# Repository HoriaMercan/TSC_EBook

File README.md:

## Horia Mercan - OpenBook - Systems Testing

This project presents the electronic design (schematic/pcb) and the visual design of a complete ebook. 

## Hardware Modules and Components

**ESP32-C6-WROOM-1-N8 – Main Microcontroller:**
* Power Supply: 3.3V.
* Communications: SPI, I2C, UART, GPIO.

We will link interfaces of each module with main controller's pins:

**SPI ESD Protection Lines**
* Protects the SPI lines for the SD card, e-paper, external flash.

**LDO Voltage Regulator**
* Steps down the voltage from 5V to 3.3V to power the ESP32-C6 and other modules.

**SD Card Module**
* Interface: SPI
* Pins Used:
    * `SS_SD` → `IO4`
    * `MOSI` → `IO7`
    * `MISO` → `IO2`
    * `SCK` → `IO6`

**E-Paper Display**
* Interface: SPI
* Pins Used:
    * `EPD_CS` → `IO10`
    * `EPD_DC` → `IO5`
    * `EPD_RST` → `IO23`
    * `EPD_BUSY` → `IO3`
    * `MOSI`, `SCK` (shared with SD)

**RTC Module - DS3231SN**
* Interface: I2C
* Pins Used:
    * `SCL` → `IO22`
    * `SDA` → `IO21`
    * `INT_RTC` → `IO8`
    * `32KHZ` → `IO1`
    * `RTC_RST` → `IO18`

**LiPo Fuel Gauger**
* Built-in charging control.
* MAX17048G+T10
* Battery level monitoring with:
    * Battery ChargeLevel IC → I2C => `SDA`, `SCL`

**Qwiic / Stemma QT Connector**
* Communicates entirely via I2C: `SCL`/`SDA` 

**Environmental Sensor - BME688**
* Protocol: I2C (shared) => `SDA`, `SCL`

**Environmental Sensor - BME688**
* Interface: I2C (shared with RTC)
* Power Supply: 3.3V
* Pins Used:  `SDA`, `SCL`

**External Flash - NORFlash64MB**
* Interface: SPI
* Pins Used:
    * `FLASH_CS` → `IO11`
    * Rest (`MOSI`, `MISO`, `SCK`) shared

**SD/USB interface**
* `USB_D+` → `IO13`
* `USB_D-` → `IO12`

**Reset and Boot Buttons**
* `IO/BOOT` → `IO9`
* `RESET` → `EN`

**Diodes for reverse polarity protection.**

**USB-C Connector + ESD Protection**
* Main power and data input.
* Includes TVS diodes for ESD protection.

## Block components & schematic

## Communication Interfaces

| Interface | Connected Components       | ESP32-C6 Pins                       |
| :-------- | :------------------------- | :------------------------------------ |
| SPI       | SD Card, E-paper, NOR Flash | `MOSI` (`IO7`), `MISO` (`IO2`), `SCK` (`IO6`) |
| I2C       | RTC, BME688, Battery Level | `SDA` (`IO22`), `SCL` (`IO21`)        |
| UART      | Debugging / Flash          | `TX` (`GPIO16`), `RX` (`GPIO17`)        |
| GPIO      | Buttons, status signals    | `IO0` - `IO23`                        |
| USB       | PC connection / power      | `USB_D+`/`D-` (`IO13`/`IO12`)

## Energy management

| Component                   | Power Supply (V) | Estimated Current (mA) | Estimated Power (W) | Notes                                                                  |
|-----------------------------|-------------------|------------------------|----------------------|------------------------------------------------------------------------|
| ESP32-C6-WROOM-1-N8         | 3.3               | 150 (average)          | 0.5                  | Active mode; varies significantly based on usage.                       |
| SD Card Module              | 3.3               | 10 (average)           | 0.033                | Intermittent read/write operations.                                     |
| E-Paper Display             | 3.3               | 1(average)             | 0.0033               | Power used only during updates, very low average.                   |
| RTC Module - DS3231SN       | 3.3               | 1                      | 0.0033               |                                                                        |
| LiPo Fuel Gauger (MAX17048) | 3.3               | 0.05                   | 0.000165             | Very low power consumption.                                            |
| BME688 (Environmental Sensor) | 3.3               | 1 (average)            | 0.0033               | Intermittent readings.                                                  |
| NORFlash64MB (External Flash)| 3.3               | 2 (average)            | 0.0066               | Intermittent read/write operations.                                     |
| LDO Voltage Regulator       | 5 (input) / 3.3 (output) | Variable             | Variable               | Efficiency depends on load; quiescent current is very low.             |
| USB-C Connector + ESD       | 5 (input)         | Variable               | Variable               | Power depends on charging current; ESD protection negligible.          |
| Reset/Boot Buttons          | N/A               | Negligible             | Negligible           |                                                                        |
| **Total (Approximate)** |                   |          150-200              | **~0.55** | This is a rough estimate; actual power depends on duty cycles and usage. |

## Images

# BOM

| Piece Name | Piece Type | Link |
|------------|------------|------|
| SAMACSYS_PARTS_USB4110-GF-A | USB-C Connector | https://www.snapeda.com/parts/USB4110-GF-A./Global%20Connector%20Technology/view-part/ |
| ESP32_WROVER_EAGLE-LTSPICE_R | Resistor | https://componentsearchengine.com/part-view/R0402%201%25%20100%20K%20(RC0402FR-07100KL)/YAGEO |
| MAX17048G+T10 | Cell Fuel Gauge | https://www.snapeda.com/parts/MAX17048G+T10/Analog%20Devices/view-part/ |
| W25Q512JVEIQ | Flash Memory (NOR) | https://www.snapeda.com/parts/W25Q512JVEIQ/Winbond%20Electronics/view-part/?ref=search&t=W25Q512JVEIQ |
| RCL_CPOL-EU | Polarized Capacitor | https://grabcad.com/library/tantalum-smd-capacitor-type-b-3528-1 |
| ESP32-C6-WROOM-1-N8 | ESP32 Module | https://www.snapeda.com/parts/ESP32-C6-WROOM-1-N8/Espressif%20Systems/view-part/?ref=search&t=ESP32-C6-WROOM-1-N8 |
| ADAFRUIT_CHIP-LED0603 | LED | https://www.snapeda.com/parts/KP-1608SURCK/Kingbright/view-part/?ref=search&t=LED%200603 |
| ESP32_WROVER_SPARKFUN-IC-POWER_MCP73831 | Li-Ion/Li-Poly Charge Management Controller | https://componentsearchengine.com/part-view/MCP73831T-2ACI%2FOT/Microchip |
| ESP32_WROVER_BME680_BME680 | Environmental Sensor | https://www.snapeda.com/parts/BME680/Bosch%20Sensortec/view-part/?ref=search&t=bme680 |
| CPH3225A | Crystal | https://www.snapeda.com/parts/CPH3225A/Seiko/view-part/ |
| BUTTON_CUSYOMV1 | Button | https://ro.mouser.com/ProductDetail/Panasonic/EVQ-P7L01P?qs=rJ%252BziJWpyszWhhNszc02jQ%3D%3D&utm_id=6470900573&utm_source=google&utm_medium=cpc&utm_marketing_tactic=emeacorp&gad_source=1&gbraid=0AAAAADn_wf2u1-1FzOTFyljDC4WPsSKtJ&gclid=Cj0KCQjwqcO_BhDaARIsACz62vPVeStXn6lXkpk-IPhYAE7F2gpbfTm751cNxrlbJa5xGxG5NT01Z4waAqXEEALw_wcB&_gl=1*bly5rh*_ga*NDU0NzEyMTQxLjE3NDM4Nzk4OTU.*_ga_15W4STQT4T*MTc0Mzg4MTg0Ni4yLjAuMTc0Mzg4MTg0Ny41OS4wLjA. |
| FH34SRJ-24S-0.5SH_99_ | FPC Connector | https://componentsearchengine.com/part-view/FH34SRJ-24S-0.5SH(99)/Hirose |
| 744043680 | Inductor | https://eu.mouser.com/ProductDetail/Wurth-Elektronik/744043680?qs=PGXP4M47uW6VkZq%252BkzjrHA%3D%3D |
| PGB1010603MR | TVS Diode (0603) | https://www.snapeda.com/parts/PGB1010603MR/Littelfuse/view-part/ |
| SJ | 3-Way Solder Jumper | https://grabcad.com/library/solder-jumpers-1 |
| XC6220A331MR-G | Voltage Regulator | https://ro.mouser.com/ProductDetail/Torex-Semiconductor/XC6220A331MR-G?qs=AsjdqWjXhJ8ZSWznL1J0gg%3D%3D&utm_source=octopart&utm_medium=aggregator&utm_campaign=865-XC6220A331MR-G&utm_content=Torex%20Semiconductor |
| QWIIC_CONNECTOR | I²C Connector (PRT-14417) | https://www.snapeda.com/parts/PRT-14417/SparkFun/view-part/ |
| ESP32-CAP C0402 | Capacitor | https://componentsearchengine.com/part-view/CC0402MRX5R5BB106/YAGEO |
| ESP VARSISTOR | Varistor (B72520T0350K062) | https://ro.mouser.com/ProductDetail/EPCOS-TDK/B72520T0350K062?qs=dEfas%2FXlABIszF52uu7vrg%3D%3D |
| MBR0530 | Schottky Diode | https://www.snapeda.com/parts/MBR0530/Onsemi/view-part/ |
| ESP32_WROVER_SPARKFUN-DISCRETESEMI_MOSFET_PCH | MOSFET (DMG2305UX-7) | https://componentsearchengine.com/part-view/DMG2305UX-7/Diodes%20Incorporated |
| 112ATAARR03 | microSD | https://www.snapeda.com/parts/112A-TAAR-R03/Attend/view-part/ |
| ESP32_WROVER_AVX---SD0805S020S1R0 | Schottky Diode | https://componentsearchengine.com/part-view/SD0805S020S1R0/Kyocera%20AVX |
| DS3231SN# | I²C-Integrated RTC/TCXO/Crystal | https://www.snapeda.com/parts/DS3231SN%23/Analog%20Devices/view-part/?ref=search&t=DS3231SN%23 |
| BD5229G-TR | Voltage Detector | https://www.snapeda.com/parts/BD5229G-TR/Rohm/view-part/?ref=search&t=BD5229G-TR |
| SI1308EDL-T1-GE3 | MOSFET Transistor | https://www.snapeda.com/parts/SI1308EDL-T1-GE3/Vishay/view-part/ |
| TP | Test Pad | none |
| USBLC6-2SC6Y | TVS Diode | https://www.snapeda.com/parts/USBLC6-2SC6Y/STMicroelectronics/view-part/?ref=dk&t=USBLC6-2SC6Y&con_ref=None |

# ESP32 Pins Usage

**ESP32-C6 Pins and Functions**

| Pin | Signal | Describtion |
| :--- | :--- | :--- |
| 16 | RTC\_RST | RTC Reset |
| 17 | I2C\_PW | I2C Power Supply |
| 18 | EPD\_3V3\_C | 3.3V to EPD |
| 19 | SDA | I2C Data Line |
| 20 | SCL | I2C Clock Line |
| 21 | EPD\_RST | EPD (E-paper display) Reset |
| 23 | IO/CHANGE | State Change Signal |
| 24 | RX | UART Receive Line |
| 25 | TX | UART Transmit Line |
| 26 | EPD\_BUSY | EPD  Status |
| 27 | MISO | SPI Controller In Peripheral Out Line |
| 3 | RESET | Reset Circuit |
| 4 | SS\_SD | SD Card Chip Select |
| 5 | EPD\_DC | EPD (E-paper display) Data/Command Pin |
| 6 | SCK | SPI Clock Line |
| 7 | MOSI | SPI Controller Out Peripheral In Line |
| 8 | INT\_RTC | RTC Interrupt Signal |
| 9 | 32KHZ | 32 kHz Oscillator |
| 11 | IO10 | GPIO |
| 12 | IO11 | GPIO |
| 13 | IO12 | GPIO |
| 14 | IO13 | GPIO |
| 15 | IO/BOOT | Boot/Flash Button |

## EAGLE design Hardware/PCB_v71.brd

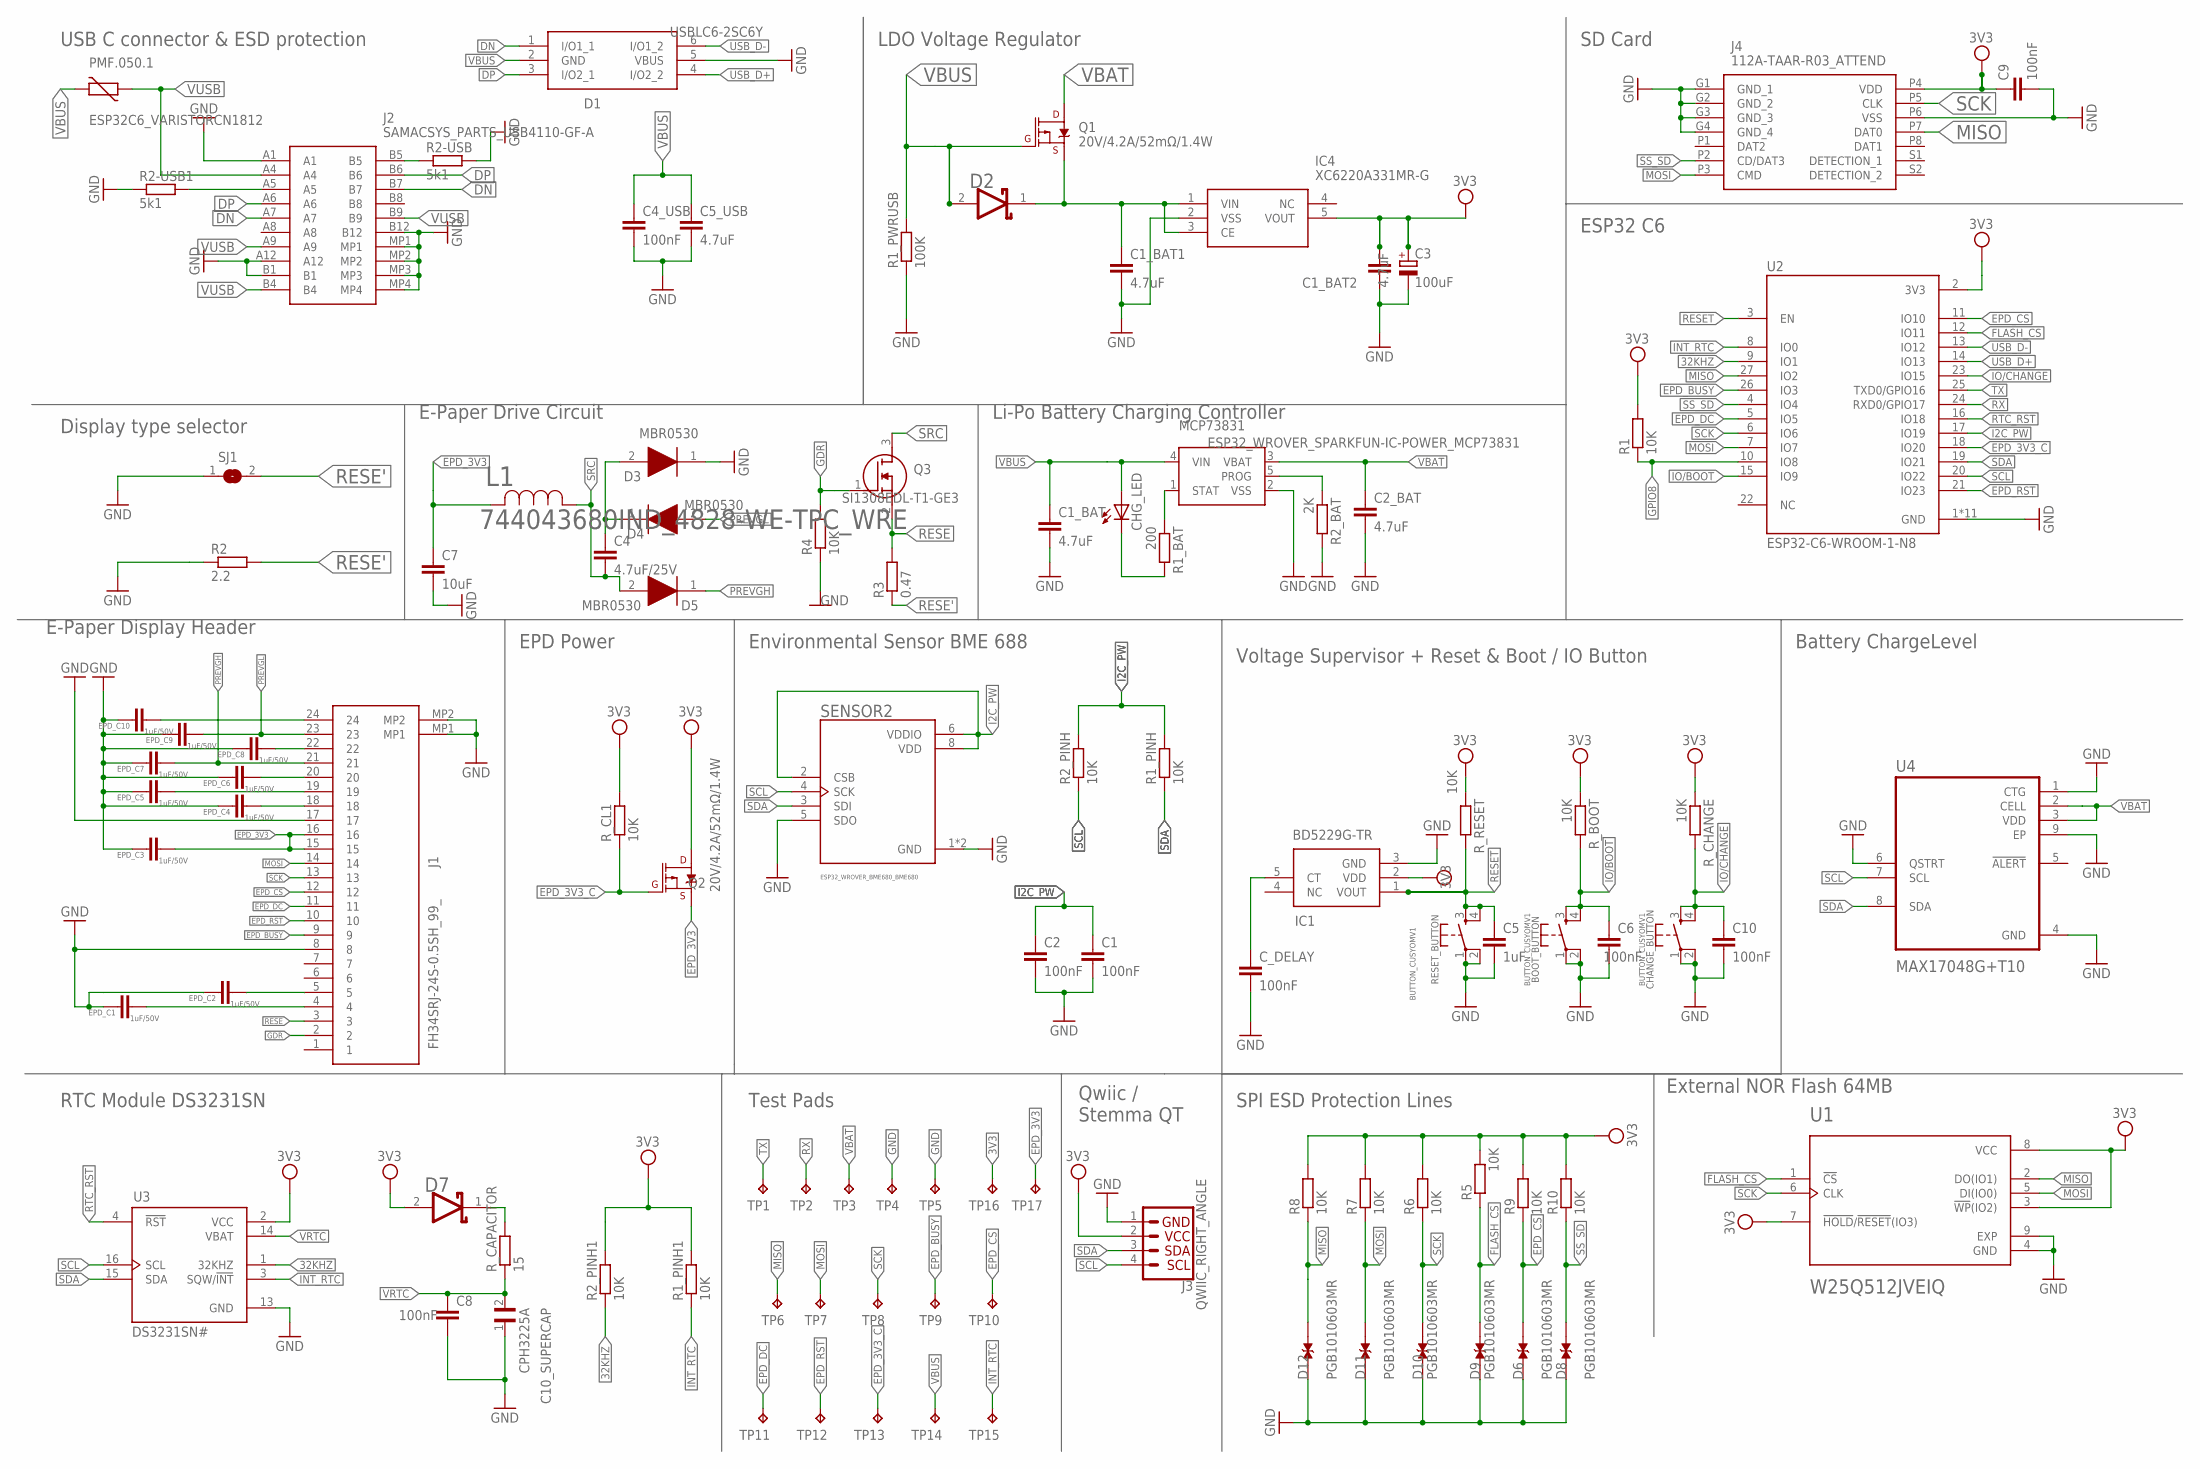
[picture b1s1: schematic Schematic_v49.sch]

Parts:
BOOT_BUTTON: BUTTON_CUSYOMV1; MYBUTTON
C1, C2, C4_USB, C6, C8, C9, C10: 100nF; EAGLE-LTSPICE_C0402
C1_BAT, C1_BAT1, C1_BAT2, C2_BAT, C5_USB: 4.7uF; EAGLE-LTSPICE_C0402
C3: 100uF; RCL_CT3528
C4: 4.7uF/25V; EAGLE-LTSPICE_C0402
C5: 1uF; EAGLE-LTSPICE_C0402
C7: 10uF; EAGLE-LTSPICE_C0402
C10_SUPERCAP: CPH3225A; CAPCP3225X100N
CHANGE_BUTTON: BUTTON_CUSYOMV1; MYBUTTON
CHG_LED: ADAFRUIT_LEDCHIP-LED0603; ADAFRUIT_CHIP-LED0603
C_DELAY: 100nF; EAGLE-LTSPICE_C0402
D1: USBLC6-2SC6Y; SOT95P280X145-6N
D2, D7: ESP32_WROVER_AVX---SD0805S020S1R0_AVX_SD0805S020S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; ESP32_WROVER_AVX---SD0805S020S1R0_AVX_SD0805S020S1R0_0
D3, D4, D5: MBR0530; SOD3716X135N
D6, D8, D9, D10, D11, D12: PGB1010603MR; DIOC1608X36N
EPD_C1, EPD_C2, EPD_C3, EPD_C4, EPD_C5, EPD_C6, EPD_C7, EPD_C8, EPD_C9, EPD_C10: 1uF/50V; EAGLE-LTSPICE_C0402
IC1: BD5229G-TR; SOT95P280X125-5N
IC4: XC6220A331MR-G; SOT95P280X125-5N
J1: FH34SRJ-24S-0.5SH_99_; FH34SRJ24S05SH99
J2: SAMACSYS_PARTS_USB4110-GF-A; SAMACSYS_PARTS_USB4110GFA
J3: QWIIC_RIGHT_ANGLE; JST04_1MM_RA
J4: 112A-TAAR-R03_ATTEND; 112ATAARR03ATTEND
L1: 744043680IND_4828-WE-TPC_WRE; IND_4828-WE-TPC_WRE
MCP73831: ESP32_WROVER_SPARKFUN-IC-POWER_MCP73831; ESP32_WROVER_SPARKFUN-IC-POWER_SOT23-5
PMF.050.1: ESP32C6_VARISTORCN1812; ESP32C6_VARISTOR_CT/CN1812
Q1, Q2: 20V/4.2A/52mΩ/1.4W; ESP32_WROVER_SPARKFUN-DISCRETESEMI_SOT23-3
Q3: SI1308EDL-T1-GE3; SOT65P210X110-3N
R1, R1_PINH, R1_PINH1, R2_PINH, R2_PINH1, R4, R5, R6, R7, R8, R9, R10: 10K; ESP32_WROVER_EAGLE-LTSPICE_R0402
R1_BAT: 200; ESP32_WROVER_EAGLE-LTSPICE_R0402
R1_PWRUSB: 100K; ESP32_WROVER_EAGLE-LTSPICE_R0402
R2: 2.2; ESP32_WROVER_EAGLE-LTSPICE_R0402
R2-USB, R2-USB1: 5k1; ESP32_WROVER_EAGLE-LTSPICE_R0402
R2_BAT: 2K; ESP32_WROVER_EAGLE-LTSPICE_R0402
R3: 0.47; ESP32_WROVER_EAGLE-LTSPICE_R0402
RESET_BUTTON: BUTTON_CUSYOMV1; MYBUTTON
R_BOOT: 10K; ESP32_WROVER_EAGLE-LTSPICE_R0402
R_CAPACITOR: 15; ESP32_WROVER_EAGLE-LTSPICE_R0402
R_CHANGE: 10K; ESP32_WROVER_EAGLE-LTSPICE_R0402
R_CL1: 10K; ESP32_WROVER_EAGLE-LTSPICE_R0402
R_RESET: 10K; ESP32_WROVER_EAGLE-LTSPICE_R0402
SENSOR2: ESP32_WROVER_BME680_BME680; ESP32_WROVER_BME680_PSON80P300X300X100-8N
SJ1: SJ
TP1, TP2, TP3, TP4, TP5, TP6, TP7, TP8, TP9, TP10, TP11, TP12, TP13, TP14, TP15, TP16, TP17: TPTP20R; TP20R
U1: W25Q512JVEIQ; SON127P600X800X80-9N
U2: ESP32-C6-WROOM-1-N8; XCVR_ESP32-C6-WROOM-1-N8
U3: DS3231SN#; SOIC127P1032X265-16N
U4: MAX17048G+T10; SON50P200X200X80-9N

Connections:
3V3: C1_BAT2.1, C3.+, C9.1, D7.2 (ANODE), IC1.2 (VDD), IC4.5 (VOUT), J3.2, J4.P4 (VDD), Q2.3 (D), R1.2, R1_PINH1.2, R2_PINH1.2, R5.2, R6.2, R7.2, R8.2, R9.2, R10.2, R_BOOT.1, R_CHANGE.1, R_CL1.2, R_RESET.1, TP16.TP, U1.3 (!WP!(IO2)), U1.7 (!HOLD!/!RESET!(IO3)), U1.8 (VCC), U2.2 (3V3), U3.2 (VCC)
32KHZ: R2_PINH1.1, U2.9 (IO1), U3.1 (32KHZ)
DN: D1.1 (I/O1_1), J2.A7, J2.B7
DP: D1.3 (I/O2_1), J2.A6, J2.B6
EPD_3V3: C7.1, EPD_C3.2, J1.15, J1.16, L1.2, Q2.2 (S), TP17.TP
EPD_3V3_C: Q2.1 (G), R_CL1.1, TP13.TP, U2.18 (IO20)
EPD_BUSY: J1.9, TP9.TP, U2.26 (IO3)
EPD_CS: D6.2, J1.12, R9.1, TP10.TP, U2.11 (IO10)
EPD_DC: J1.11, TP11.TP, U2.5 (IO5)
EPD_RST: J1.10, TP12.TP, U2.21 (IO23)
FLASH_CS: D9.2, R5.1, U1.1 (!CS), U2.12 (IO11)
GDR: J1.2, Q3.1 (G), R4.2
GND: BOOT_BUTTON.1, BOOT_BUTTON.2, C1.2, C1_BAT.2, C1_BAT1.2, C1_BAT2.2, C2.2, C2_BAT.2, C3.-, C4_USB.2, C5.2, C5_USB.2, C6.2, C7.2, C8.2, C9.2, C10.2, C10_SUPERCAP.1, CHANGE_BUTTON.1, CHANGE_BUTTON.2, C_DELAY.2, D1.5 (VBUS), D3.1 (K), D6.1, D8.1, D9.1, D10.1, D11.1, D12.1, EPD_C1.1, EPD_C2.1, EPD_C3.1, EPD_C4.1, EPD_C5.1, EPD_C6.1, EPD_C7.1, EPD_C8.1, EPD_C9.1, EPD_C10.1, IC1.3 (GND), IC4.2 (VSS), J1.8, J1.17, J1.MP1, J1.MP2, J2.A1, J2.A12, J2.B1, J2.B12, J2.MP1, J2.MP2, J2.MP3, J2.MP4, J3.1, J4.G1 (GND_1), J4.G2 (GND_2), J4.G3 (GND_3), J4.G4 (GND_4), J4.P6 (VSS), MCP73831.2 (VSS), R1_PWRUSB.1, R2.1, R2-USB.2, R2-USB1.1, R2_BAT.2, R4.1, RESET_BUTTON.1, RESET_BUTTON.2, SENSOR2.1 (GND), SENSOR2.5 (SDO), SENSOR2.7 (GND), SJ1.1, TP4.TP, TP5.TP, U1.4 (GND), U1.9 (EXP), U2.1 (GND), U2.28 (GND), U2.29_1 (GND), U2.29_2 (GND), U2.29_3 (GND), U2.29_4 (GND), U2.29_5 (GND), U2.29_6 (GND), U2.29_7 (GND), U2.29_8 (GND), U2.29_9 (GND), U3.13 (GND), U4.1 (CTG), U4.4 (GND), U4.6 (QSTRT), U4.9 (EP)
GPIO8: R1.1, U2.10 (IO8)
I2C_PW: C1.1, C2.1, R1_PINH.2, R2_PINH.2, SENSOR2.2 (CSB), SENSOR2.6 (VDDIO), SENSOR2.8 (VDD), U2.17 (IO19)
INT_RTC: R1_PINH1.1, TP15.TP, U2.8 (IO0), U3.3 (SQW/!INT)
IO/BOOT: BOOT_BUTTON.3, BOOT_BUTTON.4, C6.1, R_BOOT.2, U2.15 (IO9)
IO/CHANGE: C10.1, CHANGE_BUTTON.3, CHANGE_BUTTON.4, R_CHANGE.2, U2.23 (IO15)
MISO: D12.2, J4.P7 (DAT0), R8.1, TP6.TP, U1.2 (DO(IO1)), U2.27 (IO2)
MOSI: D11.2, J1.14, J4.P3 (CMD), R7.1, TP7.TP, U1.5 (DI(IO0)), U2.7 (IO7)
unnamed: J2.A5, R2-USB1.2
unnamed: J2.B5, R2-USB.1
unnamed: D7.1 (CATHODE), R_CAPACITOR.2
unnamed: C1_BAT1.1, D2.1 (CATHODE), IC4.1 (VIN), IC4.3 (CE), Q1.2 (S)
unnamed: C4.1, D3.2 (A), D4.1 (K)
unnamed: CHG_LED.C, R1_BAT.2
unnamed: MCP73831.1 (STAT), R1_BAT.1
unnamed: EPD_C2.2, J1.5
unnamed: MCP73831.5 (PROG), R2_BAT.1
unnamed: EPD_C1.2, J1.4
unnamed: C_DELAY.1, IC1.5 (CT)
unnamed: EPD_C4.2, J1.18
unnamed: EPD_C5.2, J1.19
unnamed: EPD_C6.2, J1.20
unnamed: EPD_C8.2, J1.22
unnamed: EPD_C10.2, J1.24
PREVGH: D5.1 (K), EPD_C7.2, J1.21
PREVGL: D4.2 (A), EPD_C9.2, J1.23
RESE: J1.3, Q3.2 (S), R3.2
RESE': R2.2, R3.1, SJ1.2
RESET: C5.1, IC1.1 (VOUT), RESET_BUTTON.3, RESET_BUTTON.4, R_RESET.2, U2.3 (EN)
RTC_RST: U2.16 (IO18), U3.4 (!RST)
RX: TP2.TP, U2.24 (RXD0/GPIO17)
SCK: D10.2, J1.13, J4.P5 (CLK), R6.1, TP8.TP, U1.6 (CLK), U2.6 (IO6)
SCL: J3.4, R2_PINH.1, SENSOR2.4 (SCK), U2.20 (IO22), U3.16 (SCL), U4.7 (SCL)
SDA: J3.3, R1_PINH.1, SENSOR2.3 (SDI), U2.19 (IO21), U3.15 (SDA), U4.8 (SDA)
SRC: C4.2, D5.2 (A), L1.1, Q3.3 (D)
SS_SD: D8.2, J4.P2 (CD/DAT3), R10.1, U2.4 (IO4)
TX: TP1.TP, U2.25 (TXD0/GPIO16)
USB_D+: D1.4 (I/O2_2), U2.14 (IO13)
USB_D-: D1.6 (I/O1_2), U2.13 (IO12)
VBAT: C2_BAT.1, MCP73831.3 (VBAT), Q1.3 (D), TP3.TP, U4.2 (CELL), U4.3 (VDD)
VBUS: C1_BAT.1, C4_USB.1, C5_USB.1, CHG_LED.A, D1.2 (GND), D2.2 (ANODE), MCP73831.4 (VIN), PMF.050.1.2, Q1.1 (G), R1_PWRUSB.2, TP14.TP
VRTC: C8.1, C10_SUPERCAP.2, R_CAPACITOR.1, U3.14 (VBAT)
VUSB: J2.A4, J2.A9, J2.B4, J2.B9, PMF.050.1.1

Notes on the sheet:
USB C connector & ESD protection
LDO Voltage Regulator
SD Card
Display type selector
E-Paper Drive Circuit
Li-Po Battery Charging Controller
ESP32 C6
E-Paper Display Header
EPD Power
Environmental Sensor BME 688
Voltage Supervisor + Reset & Boot / IO Button
Battery ChargeLevel
RTC Module DS3231SN
Test Pads
Qwiic / Stemma QT
SPI ESD Protection Lines
External NOR Flash 64MB

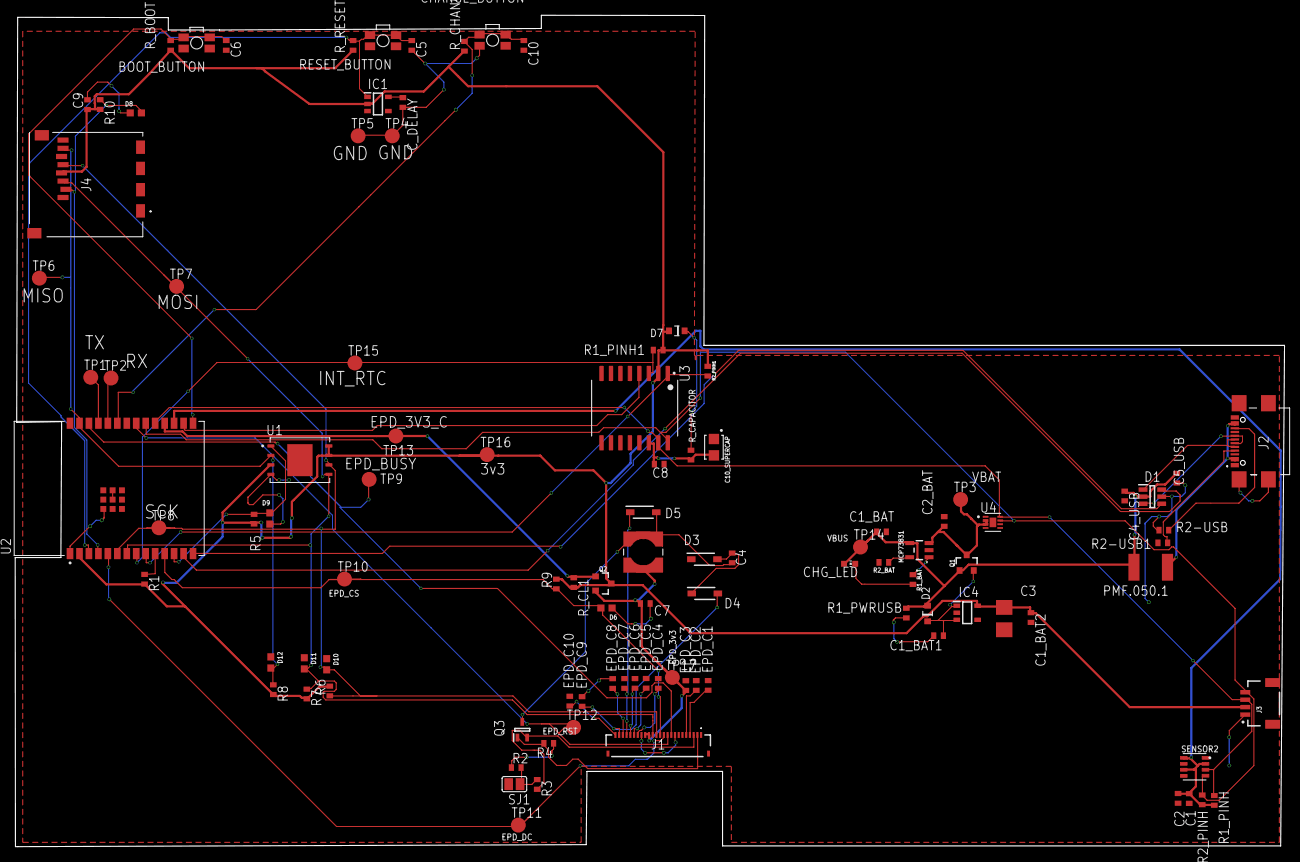
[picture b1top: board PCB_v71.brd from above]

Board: 2 copper layers, 170.3 x 111.6 mm, 103 parts (0 on the bottom side), 55 nets.

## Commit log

2025-04-04 Create LICENSE
2025-04-05 Update LICENSE
2025-04-05 add project
2025-04-05 readme added. schema added
2025-04-06 Add OpenBook with battery connected
2025-04-06 OpenBook with connected battery
2025-04-06 Delete Mechanical/OpenBook Enclosure v16.rar
    Deleted rar. Added .zip file
2025-04-06 updated readme. added pins usage for esp32
2025-04-14 Updated PCB: Fixed values layer & thickness. Changed block scheme

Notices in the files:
parts and their libraries:
COPYRIGHT: Copyright (C) 2024 Ultra Librarian. All rights reserved.
